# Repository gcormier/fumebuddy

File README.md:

# FumeBuddy
FumeBuddy is an ESP32 replacement for the switch housing on the Hakko FX-950, FX-951 and FX-952. Out of the box, it was designed to toggle a fume extractor via a smart switch flashed with [Tasmota](https://tasmota.github.io/docs/#/). It is powered via USB, which allows it to be powered by a battery pack if desired.

## Design Goals
- Easily hacked
- Replace stock housing
- Default behavior when un-powered

## Video
[See FumeBuddy explained and in action](https://www.youtube.com/watch?v=eo5WyHWy1So)

## Hardware Installation
- Remove the old housing
- Transfer the spring from the old housing to the new housing
- Install using the old screws
- If you'd like the manual capacitive touch function and did not order it, you can solder a single wire to the appropriate jumper

## Configuration
FumeBuddy now uses [esphome](https://esphome.io/index.html). You don't need Home Assistant or any sort of smart home. It merely eliminates the need for me to do any custom coding.

When you plug in the device, it will create it's own WiFi access point named `FumebuddyFallback` (Password is `fumebuddy`). You
can connect to this and it will redirect you to a captive portal where you can enter your WiFi credentials. Once you do this, it will reboot and connect to your WiFi. You can then access it via the IP address it was assigned by your router.

Accessing it via the IP address will give you a web interface where you can configure the device. Notably the 2 URL's that should be called when the iron is lifted and put back down.

The touch sensor threshold can be adjusted. The default is 250, but you can enable the sensitivity debug mode and view the output
in the web console to see which value works best for you.

## Operation
- If FumeBuddy is NOT powered, the iron will work as it did before with sleep function
- If FumeBuddy is powered via the 5V USB port, it will work based on what is programmed. By default, it will turn the plug ON when the iron is lifted. It will turn the plug OFF 5 seconds after the iron is put back
- Manual on/off can be by touching and holding the capacitive wire on top of the housing. It will keep the fan on until you touch it again.

## Pricing
The BOM cost alone for the product is around 23USD, which is rather expensive. I order **genuine** parts from 1st party distributors in Canada, which in this case includes Omron switches, solid state relays and the ESP32. I did not go cheap on this as owners of Hakko's are likely looking for quality components throughout. The rest includes my labor costs to assembly, flash and test the unit. As it is open sourced, you are welcome to build your own! You can cheap out on some components if you'd like. Knockoff relays and omitting the audio buzzer will save you a few dollars.

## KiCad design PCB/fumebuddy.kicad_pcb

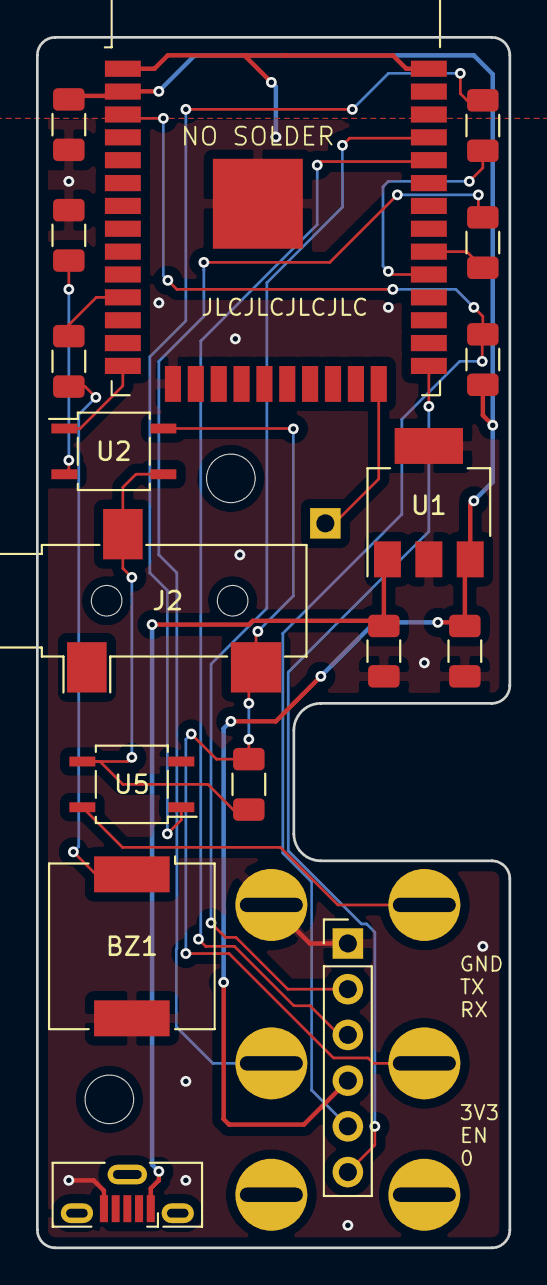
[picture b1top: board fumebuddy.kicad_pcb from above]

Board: 2 copper layers, 26.2 x 67.2 mm, 20 parts (0 on the bottom side), 19 nets.

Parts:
BZ1: Buzzer; Buzzer_CUI_CPT-9019S-SMT
C1, C2: 4.7uF; C_1206_3216Metric
C3: 10uF; C_1206_3216Metric
J1: USB_B_Micro; USB_Micro-B_Molex-105133-0001
J2: STATION; Jack_3.5mm_CUI_SJ-3523-SMT_Horizontal
J3: esp32buddy; PinHeader_1x06_P2.54mm_Vertical
J4: TOUCH; PinHeader_1x01_P2.54mm_Vertical
R1, R2, R4, R5: 4k7; R_1206_3216Metric
R3: 1k; R_1206_3216Metric
R6: 100k; R_1206_3216Metric
SW1, SW2: SW_SPDT; OMRON_SS-01-E
U1: AP7361C-33E; SOT-223-3_TabPin2
U2: CPC1017N (NO); SOP-4_3.8x4.1mm_P2.54mm
U4: ESP32-WROOM-32D; ESP32-WROOM-32
U5: CPC1117N (NC); SOP-4_3.8x4.1mm_P2.54mm

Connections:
+3V3: C2.1, C3.2, J3.4, R6.2, U1.3, U4.2
/EN: J3.5, R6.1, U4.3
/GPIO0: J3.6, U4.25
/RELAY_NC: R4.1, U4.29
/RELAY_NO: U2.1, U4.14
/RXD: J3.3, U4.34
/SENSOR: R1.1, U4.30
/TOUCH: J4.1, U4.24
/TXD: J3.2, U4.35
GND: BZ1.2, C1.1, C2.2, C3.1, J1.5, J3.1, R2.1, SW2.1, U1.2, U4.1, U4.15, U4.38, U4.39, U5.2
unnamed: BZ1.1, R3.1
unnamed: J2.R, R5.1, U2.3, U5.3
unnamed: J2.T, R5.2, SW1.2, U2.4
unnamed: R1.2, SW2.2
unnamed: R2.2, U2.2
unnamed: R3.2, U4.11
unnamed: R4.2, U5.1
unnamed: SW1.1, U5.4
VBUS: C1.2, J1.1, U1.1

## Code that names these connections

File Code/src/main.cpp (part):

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#define AUX_SAVED     "/fumebuddy_save"

// Fumebuddy Definitions
#define GPIO_SENSOR         18
#define GPIO_RELAY_AUX      14
#define GPIO_RELAY_NC       5
#define GPIO_RELAY_NO       12
#define GPIO_BUZZER         26
#define TOUCH_INPUT         T2
#define TOUCH_THRESHOLD     50
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
bool readHookState()
{
  return digitalRead(GPIO_SENSOR);
}

void startExternalDevice()
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
void stopHeater()
{
  digitalWrite(GPIO_RELAY_NO, HIGH);
}

void startHeater()
{
    digitalWrite(GPIO_RELAY_NO, LOW);
}

String loadParams(AutoConnectAux &aux, PageArgument &args)
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  SPIFFS.begin();

  // Fumebuddy setup
  pinMode(GPIO_RELAY_NO, OUTPUT);
  pinMode(GPIO_RELAY_NC, OUTPUT);
  pinMode(GPIO_SENSOR, INPUT_PULLUP);
  pinMode(GPIO_RELAY_AUX, OUTPUT);

  // This is a bodge for GPIO25 on rev 3 versions of the board, so we don't affect the actual touch input of GPIO27.
  //pinMode(25, INPUT);

  stopHeater();
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
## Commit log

2019-03-31 gitignore
2019-03-31 vmicro exclusion
2019-03-31 Initial release.
2019-03-31 touchup
2019-03-31 should be v3
2019-03-31 images
2019-03-31 docs
2019-03-31 format
2019-03-31 iframe
2019-04-03 pio git ignore
2019-10-04 Maybe update to new AutoConnect format?
2019-10-07 Revamp all code
2019-12-15 Move to one-sided for all SMD components
2019-12-16 finalize singleside
2019-12-23 still busted
2019-12-24 working!
2020-01-01 Change GPIO25 to 27 to use touch functionality
2020-01-02 Touch support to toggle fan on/off
2020-01-02 dunno what this file is but why not
2020-01-02 ignore backup sch
2020-01-02 Update schematic to use touch pin
2020-01-02 beautify
2020-01-25 ibom
2020-01-26 oops
2020-02-29 docmentatino update
2020-02-29 more docs
2020-02-29 documentation
2020-03-01 parameters for delay and beeper
2020-03-04 here we go
2020-07-03 adding debounce for onhook
2020-07-03 fixes
2020-07-03 v5 final sent to fab
2020-07-03 touch override info
2020-07-03 store info
2020-07-03 Update ibom
2020-07-14 Fix issues with new autoconnect and set defualt ssid/password
2020-07-14 Update default values for beeper/override
2020-07-14 remove partitions
2020-07-16 updated portal ssid/psk
2020-07-16 Change programming header, no more flash header
2021-10-25 update code to new GPIO pin for v6
2022-01-07 case
2023-06-25 esphome
2023-11-13 use esphome
2023-11-13 vars
2023-11-13 formatting
2023-11-13 posts
2023-11-13 fix case
2023-11-13 fix case2
2024-01-07 much updates
2024-01-07 image
